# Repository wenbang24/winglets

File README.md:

# winglets
the endgame portability keyboard

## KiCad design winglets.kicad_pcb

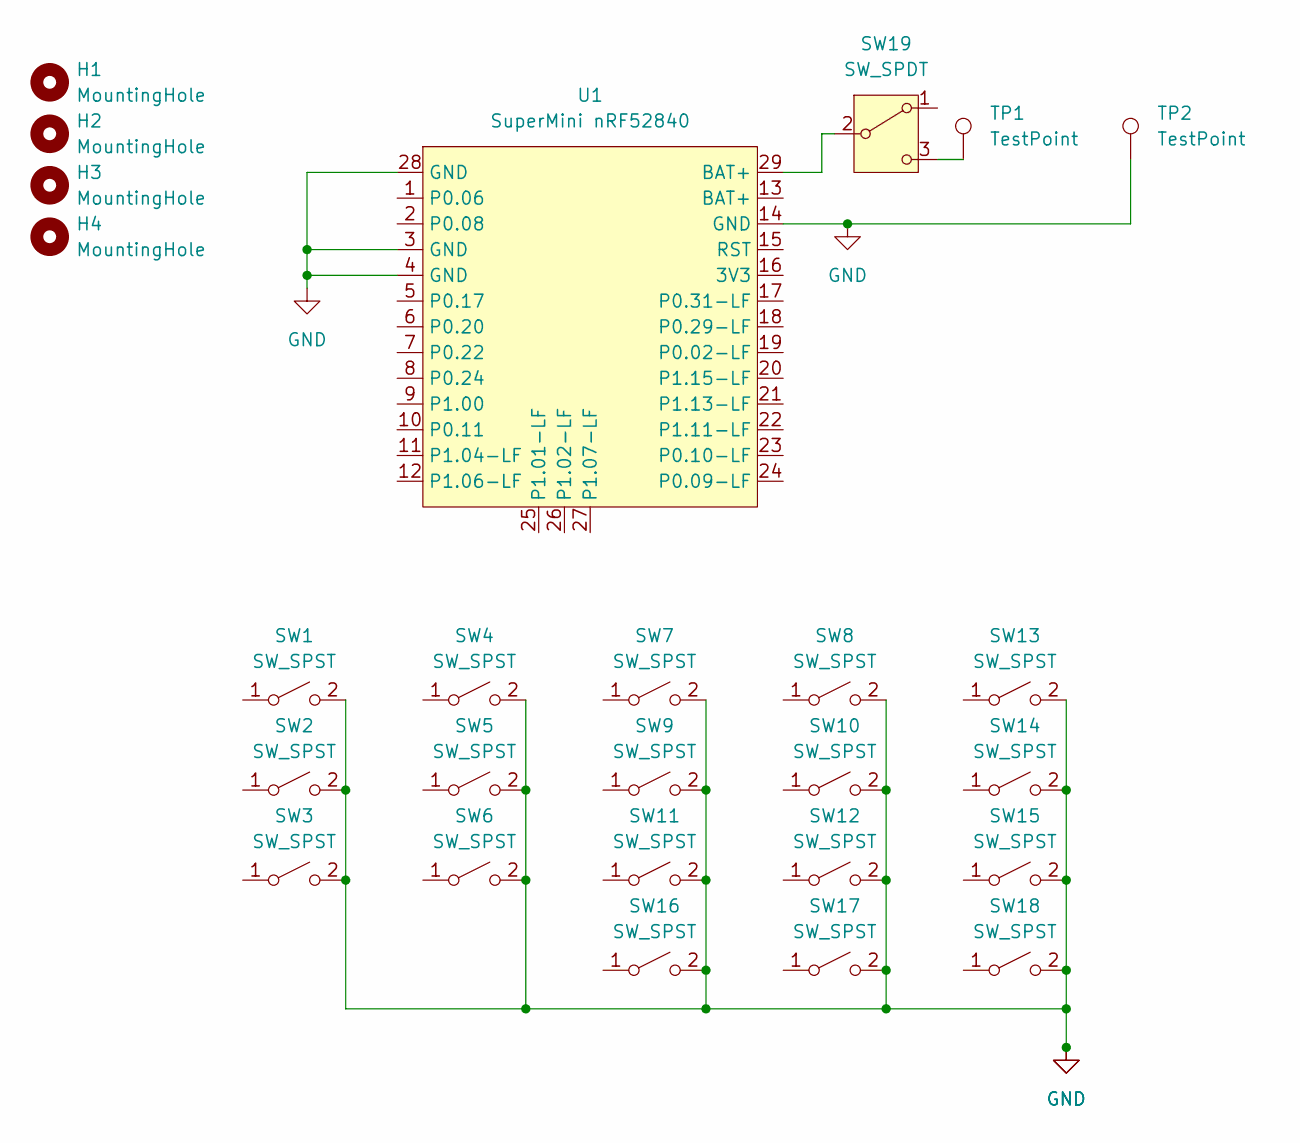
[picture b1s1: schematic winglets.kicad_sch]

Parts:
H1, H2, H3, H4: MountingHole; MountingHole_2.2mm_M2
SW1, SW2, SW3, SW4, SW5, SW6, SW7, SW8, SW9, SW10, SW11, SW12, SW13, SW14, SW15, SW16, SW17, SW18: SW_SPST; CPG1316S01D02_reversible
SW19: SW_SPDT; SW-SMD_MSK12CO2
TP1, TP2: TestPoint; TestPoint_Pad_2.5x2.5mm
U1: SuperMini nRF52840; ProMicro_flipped

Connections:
GND: SW1.2 (B), SW2.2 (B), SW3.2 (B), SW4.2 (B), SW5.2 (B), SW6.2 (B), SW7.2 (B), SW8.2 (B), SW9.2 (B), SW10.2 (B), SW11.2 (B), SW12.2 (B), SW13.2 (B), SW14.2 (B), SW15.2 (B), SW16.2 (B), SW17.2 (B), SW18.2 (B), TP2.1, U1.3 (GND), U1.4 (GND), U1.14 (GND), U1.28 (GND)
unnamed: SW19.2 (B), U1.29 (BAT+)
unnamed: SW19.3 (C), TP1.1

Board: 2 copper layers, 26 parts (0 on the bottom side), 3 nets, no tracks yet.

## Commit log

2025-11-25 schematic v1
2025-11-25 readme
2025-11-25 footprints
2025-11-28 layout v1
2025-11-28 new layout, new schematic, new footprints, new everything really
